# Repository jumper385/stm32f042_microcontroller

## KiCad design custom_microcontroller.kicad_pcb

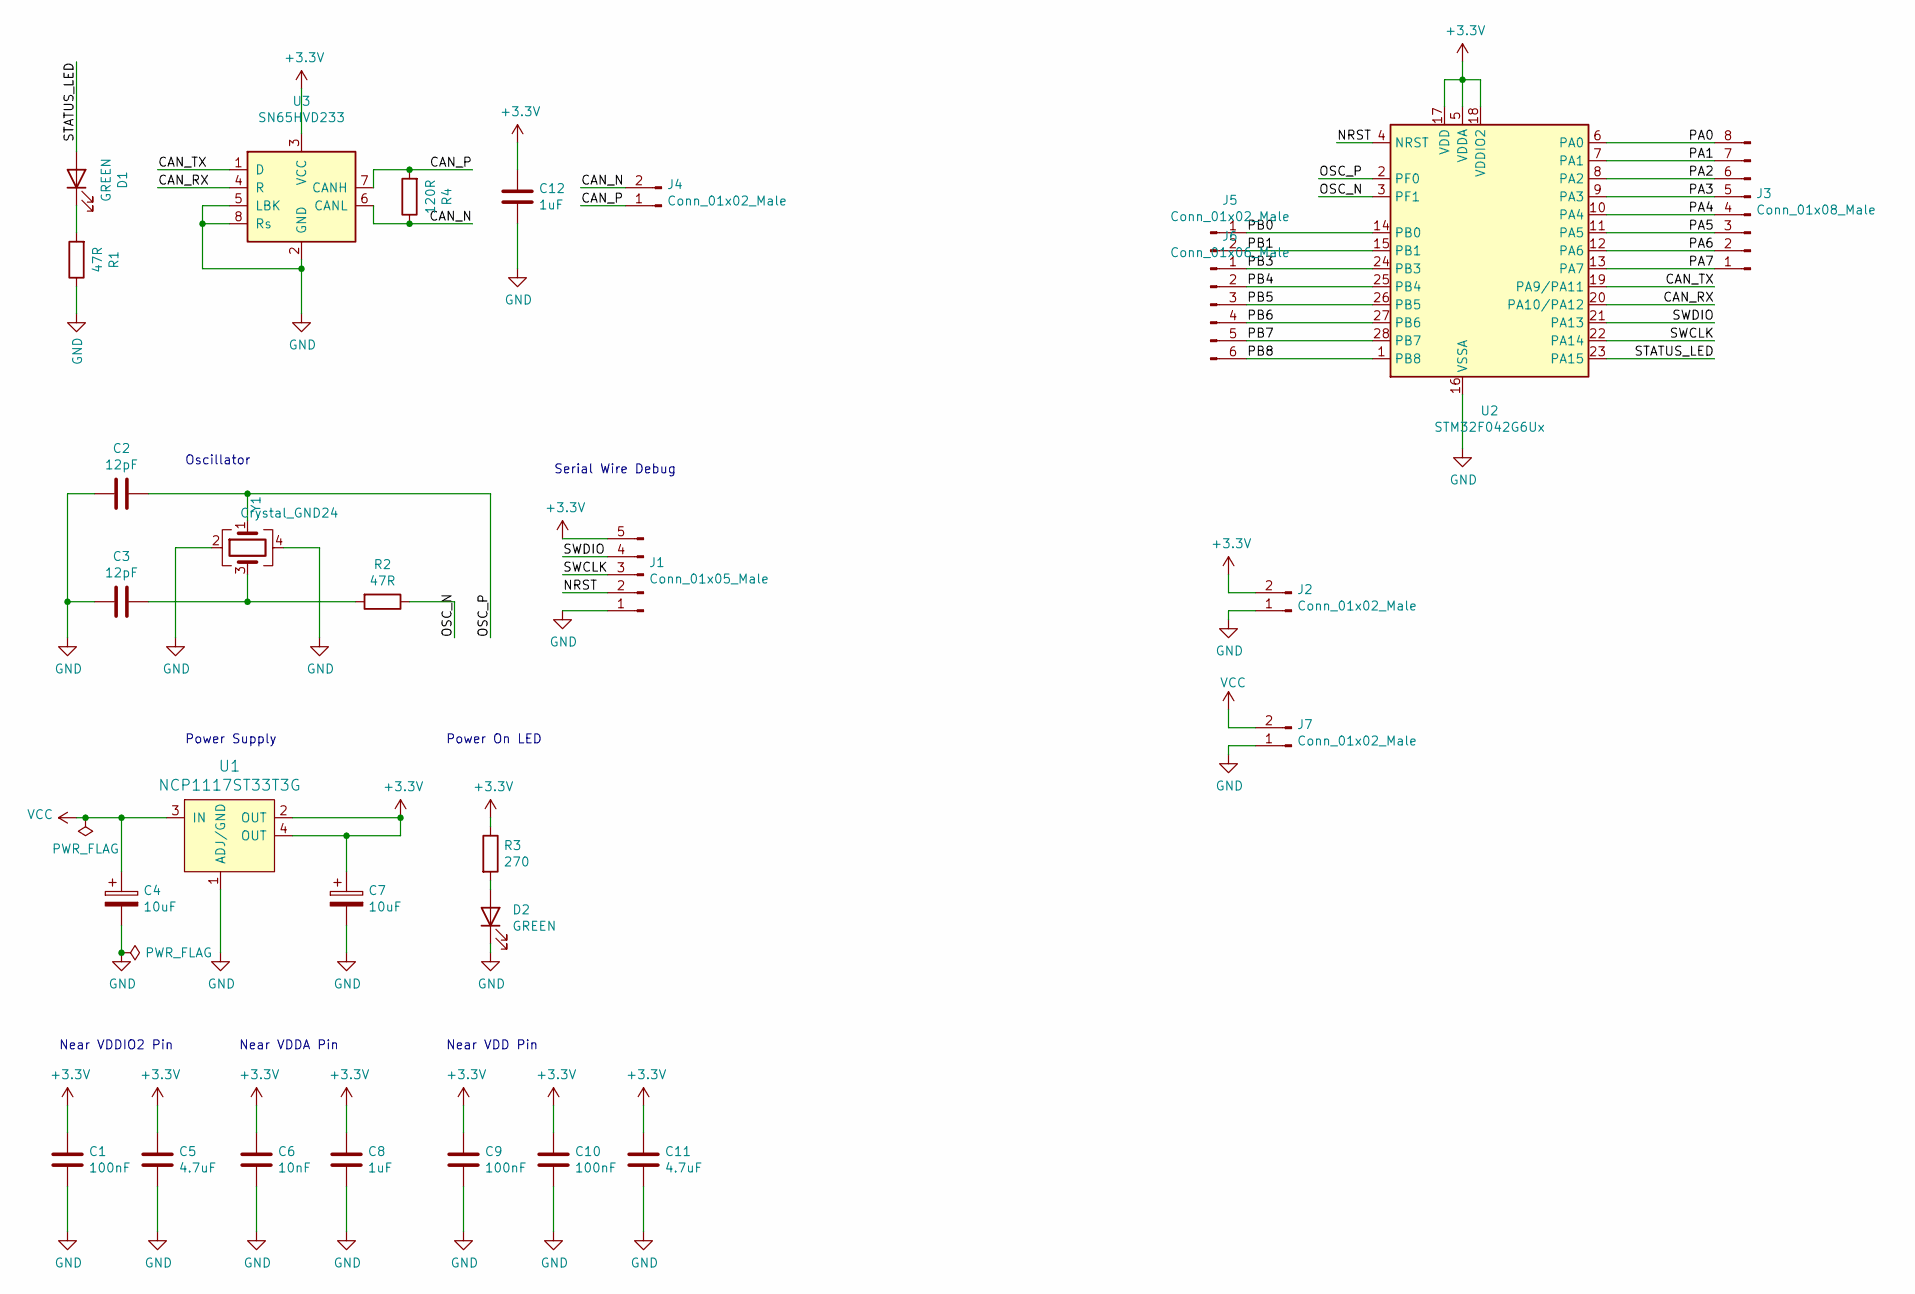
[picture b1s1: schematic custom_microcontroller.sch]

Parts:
C1, C9, C10: 100nF; C_0805_2012Metric_Pad1.15x1.40mm_HandSolder
C2, C3: 12pF; C_0805_2012Metric_Pad1.15x1.40mm_HandSolder
C4, C7: 10uF; CP_EIA-3216-18_Kemet-A_Pad1.58x1.35mm_HandSolder
C5, C11: 4.7uF; C_0805_2012Metric_Pad1.15x1.40mm_HandSolder
C6: 10nF; C_0805_2012Metric_Pad1.15x1.40mm_HandSolder
C8, C12: 1uF; C_0805_2012Metric_Pad1.15x1.40mm_HandSolder
D1, D2: GREEN; LED_0805_2012Metric_Pad1.15x1.40mm_HandSolder
J1: Conn_01x05_Male; PinHeader_1x05_P2.54mm_Horizontal
J2, J5, J7: Conn_01x02_Male; PinHeader_1x02_P2.54mm_Vertical
J3: Conn_01x08_Male; PinHeader_1x08_P2.54mm_Vertical
J4: Conn_01x02_Male; PinHeader_1x02_P2.54mm_Horizontal
J6: Conn_01x06_Male; PinHeader_1x06_P2.54mm_Vertical
R1, R2: 47R; R_0805_2012Metric_Pad1.15x1.40mm_HandSolder
R3: 270; R_0805_2012Metric_Pad1.15x1.40mm_HandSolder
R4: 120R; R_0805_2012Metric_Pad1.15x1.40mm_HandSolder
U1: NCP1117ST33T3G; SOT-223; MPN NCP1117ST33T3G; Digi-Key_PN NCP1117ST33T3GOSCT-ND
U2: STM32F042G6Ux; QFN-28_4x4mm_P0.5mm
U3: SN65HVD233; SOIC-8_3.9x4.9mm_P1.27mm
Y1: Crystal_GND24; Crystal_SMD_3225-4Pin_3.2x2.5mm_HandSoldering

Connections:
+3V3: C1.1, C5.1, C6.1, C7.1, C8.1, C9.1, C10.1, C11.1, C12.1, J1.5, J2.2, R3.1, U1.2 (OUT), U1.4 (OUT), U2.5 (VDDA), U2.17 (VDD), U2.18 (VDDIO2), U3.3 (VCC)
/CAN_N: J4.2, R4.1, U3.6 (CANL)
/CAN_P: J4.1, R4.2, U3.7 (CANH)
/CAN_RX: U2.20 (PA10/PA12), U3.4 (R)
/CAN_TX: U2.19 (PA9/PA11), U3.1 (D)
/NRST: J1.2, U2.4 (NRST)
/OSC_N: R2.1, U2.3 (PF1)
/OSC_P: C2.1, U2.2 (PF0), Y1.1
/PA0: J3.8, U2.6 (PA0)
/PA1: J3.7, U2.7 (PA1)
/PA2: J3.6, U2.8 (PA2)
/PA3: J3.5, U2.9 (PA3)
/PA4: J3.4, U2.10 (PA4)
/PA5: J3.3, U2.11 (PA5)
/PA6: J3.2, U2.12 (PA6)
/PA7: J3.1, U2.13 (PA7)
/PB0: J5.1, U2.14 (PB0)
/PB1: J5.2, U2.15 (PB1)
/PB3: J6.1, U2.24 (PB3)
/PB4: J6.2, U2.25 (PB4)
/PB5: J6.3, U2.26 (PB5)
/PB6: J6.4, U2.27 (PB6)
/PB7: J6.5, U2.28 (PB7)
/PB8: J6.6, U2.1 (PB8)
/STATUS_LED: D1.2 (A), U2.23 (PA15)
/SWCLK: J1.3, U2.22 (PA14)
/SWDIO: J1.4, U2.21 (PA13)
GND: C1.2, C2.2, C3.2, C4.2, C5.2, C6.2, C7.2, C8.2, C9.2, C10.2, C11.2, C12.2, D2.1 (K), J1.1, J2.1, J7.1, R1.1, U1.1 (ADJ/GND), U2.16 (VSSA), U3.2 (GND), U3.5 (LBK), U3.8 (Rs), Y1.2, Y1.4
unnamed: C3.1, R2.2, Y1.3
unnamed: D1.1 (K), R1.2
unnamed: D2.2 (A), R3.2
VCC: C4.1, J7.2, U1.3 (IN)

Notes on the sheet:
Near VDD Pin
Near VDDIO2 Pin
Near VDDA Pin
Power On LED
Power Supply
Oscillator
Serial Wire Debug

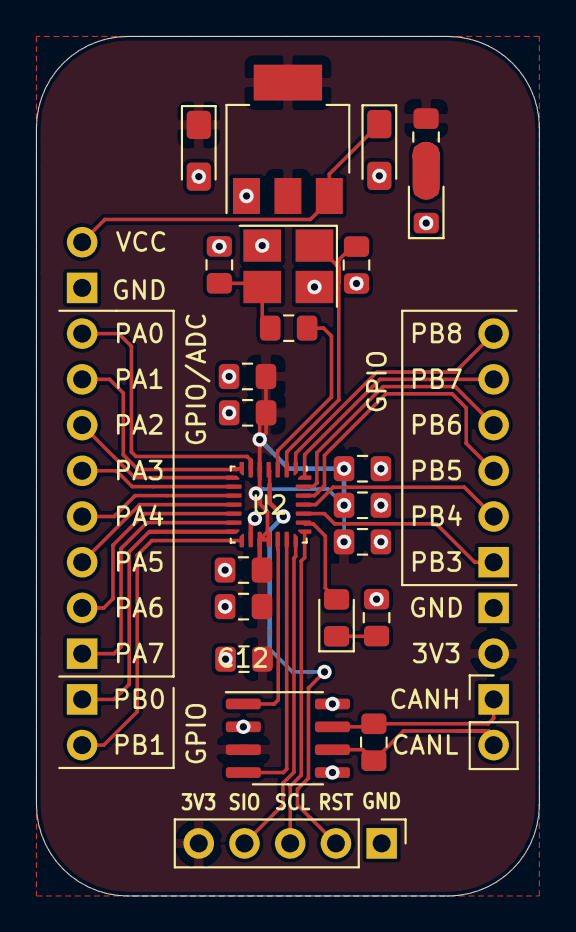
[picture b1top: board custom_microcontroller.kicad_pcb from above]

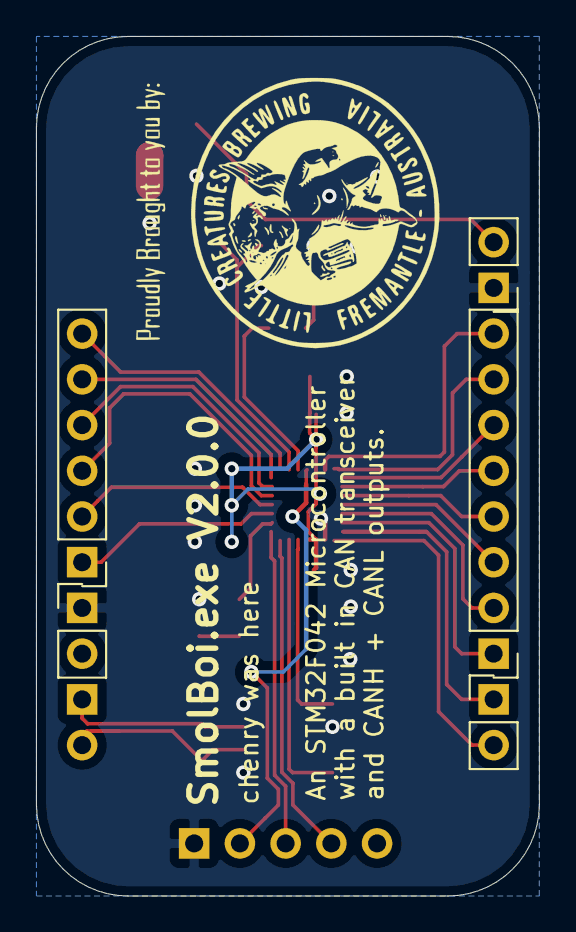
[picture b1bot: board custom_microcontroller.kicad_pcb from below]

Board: 2 copper layers, 27.9 x 47.8 mm, 29 parts (5 on the bottom side), 32 nets.

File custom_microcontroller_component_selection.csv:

Reference, Quantity, Value, Footprint, Datasheet, Category, Digi-Key_PN,Price,DK_Total,LCSC_PN,LCSC_Price,LCSC_Total
C10 C9 C1 ,3,100nF,Capacitor_SMD:C_0805_2012Metric_Pad1.15x1.40mm_HandSolder,~,Ceramic Capacitor,1276-1099-1-ND,0.15,0.45,C49678,0.0106,0.0318
C11 C5 ,2,4.7uF,Capacitor_SMD:C_0805_2012Metric_Pad1.15x1.40mm_HandSolder,~,Ceramic Capacitor,1276-1244-1-ND,0.16,0.32,C1779,0.0172,0.0344
C3 C2 ,2,12pF,Capacitor_SMD:C_0805_2012Metric_Pad1.15x1.40mm_HandSolder,~,Ceramic Capacitor,1276-2580-1-ND,0.21,0.42,C1792,0.0093,0.0186
C4 C7 ,2,10uF,Capacitor_Tantalum_SMD:CP_EIA-3216-18_Kemet-A_Pad1.58x1.35mm_HandSolder,~,Tantalum Capacitor,399-3683-1-ND,0.51,1.02,C7171,0.1549,0.3098
C6 ,1,10nF,Capacitor_SMD:C_0805_2012Metric_Pad1.15x1.40mm_HandSolder,~,Ceramic Capacitor,1276-1015-1-ND,0.15,0.15,C1710,0.0112,0.0112
C8 C12 ,2,1uF,Capacitor_SMD:C_0805_2012Metric_Pad1.15x1.40mm_HandSolder,~,Ceramic Capacitor,1276-6471-1-ND,0.15,0.3,C28323,0.0224,0.0448
D2 D1 ,2,GREEN,LED_SMD:LED_0805_2012Metric_Pad1.15x1.40mm_HandSolder,~,LED,160-1579-1-ND,0.57,1.14,C2293,0.0136,0.0272
J1 ,1,Conn_01x05_Male,Connector_PinHeader_2.54mm:PinHeader_1x05_P2.54mm_Vertical,~,Pin Header Vertical,,,0,,,0
J3 ,1,Conn_01x08_Male,Connector_PinHeader_2.54mm:PinHeader_1x08_P2.54mm_Vertical,~,Pin Header Vertical,,,0,,,0
J4 J5 J2 J7 ,4,Conn_01x02_Male,Connector_PinHeader_2.54mm:PinHeader_1x02_P2.54mm_Vertical,~,Pin Header Vertical/Horizontal,,,0,,,0
J6 ,1,Conn_01x06_Male,Connector_PinHeader_2.54mm:PinHeader_1x06_P2.54mm_Vertical,~,Pin Header Vertical,,,0,,,0
R1 R2 ,2,47R,Resistor_SMD:R_0805_2012Metric_Pad1.15x1.40mm_HandSolder,~,SMD Resistor,RMCF0805FT47R0CT-ND,0.15,0.3,C17714,0.0035,0.007
R3 ,1,270R,Resistor_SMD:R_0805_2012Metric_Pad1.15x1.40mm_HandSolder,~,SMD Resistor,RMCF0805FT270RCT-ND,0.15,0.15,C17590,0.0042,0.0042
R4 ,1,120R,Resistor_SMD:R_0805_2012Metric_Pad1.15x1.40mm_HandSolder,~,SMD Resistor,738-RMCF0805FT120RCT-ND,0.15,0.15,C17437,0.0027,0.0027
U1 ,1,NCP1117ST33T3G,Package_TO_SOT_SMD:SOT-223,https://www.onsemi.com/pub/Collateral/NCP1117-D.PDF,Linear Voltage Regulator,NCP1117ST33T3GOSCT-ND,0.67,0.67,C26537,0.2515,0.2515
U2 ,1,STM32F042G6Ux,Package_DFN_QFN:QFN-28_4x4mm_P0.5mm,http://www.st.com/st-web-ui/static/active/en/resource/techni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,STM32f042G6U6,497-17345-ND,4.18,4.18,,,0
U3 ,1,SN65HVD233,Package_SO:SOIC-8_3.9x4.9mm_P1.27mm,http://www.ti.com/lit/ds/symlink/sn65hvd234.pdf,SN65HVD233,296-35967-1-ND,4.27,4.27,C61643,1.0034,1.0034
Y1 ,1,Crystal_GND24,Crystal:Crystal_SMD_3225-4Pin_3.2x2.5mm_HandSoldering,~,16MHz Oscillator,SER4069CT-ND,0.48,0.48,C90906,0.1389,0.1389
,,,,,,,,14,,,1.8855

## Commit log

2020-10-29 panelized board
2020-10-29 added BoM w/ part selection
2020-10-29 single layer design
2020-10-29 created panelization
2020-10-29 pcb smt assembly
